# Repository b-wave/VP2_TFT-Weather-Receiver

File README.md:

# VP3-Weather-Receiver
*Davis Vantage Pro Weather Station Reciever using a Moteieino board with RFM69 and Color TFT Display.(1)*

This project is mainly a demo of the dekay/DavisRFM69 library (et.al.) @dekay using a TFT LCD screen 
it was intended to be a low-cost replacement for a broken Davis Vu Weather station that the ISS still works (with a few issues) 
*...but that is another story.* Hopefully *someone* will find this useful. I had a fun time developing it and
you can still see the saga of revisions in the source code listing as it evolved over several months. 

Display in action - Front view

Because i used a low cost Motieno, https://lowpowerlab.com/ it ran out of memory so this version
can display mainly only the data received from the Davis Vantage Vu ISS.
With some derived info like,  max and mins, rain, and cool TFT wind compass displays. 

Curently, this project version does not  add the internal data to make a complete 
TFT console replacement for display of all weather parameters. I had to remove
indoor temp, humidity and barometric pressure to make a usable replacement. 

I designed a circuit board and added some usefull features such as push button setting
a LiPo battery backup and charger, and a real time clock.  Some features will need to move to
the: *next version that uses a Teensey 3.2 board will do all this and more!*

## CREDITS:
This is a derivitive work from several authors i give credit
to the original works in line as i use them, without their work
this would not be possible.  The original work here includes the
additions for using TFT LCD displays. But I credit to getting the 
TFT to work with the RFM69 was because of this excellent article:
 https://www.pjrc.com/better-spi-bus-design-in-3-steps/  
 Thanks Paul! @PaulStoffregen

https://github.com/kobuki/VPTools
VPTools is a Davis(TM) weather station compatible transceiver library. 
It is a work in progress. It can receive from multiple RF transmitters (ISS, ATK, etc.) 
It tries to serve as a basis for similar hobby projects. 
Example sketches provide simple, parseable and RAW packet output among others.

https://github.com/dekay/DavisRFM69  By DeKay
Licence: Creative Commons Attribribution Share-Alike License http://creativecommons.org/licenses/by-sa/3.0/
This library is a modified version of the LowPowerLab's RFM69 library that enables reception of weather data 
from a Davis Instruments Integrated Sensor Suite (ISS) weather station.

https://github.com/LowPowerLab/RFM69  By Felix Rusu, LowPowerLab.com 
RFM69 library for RFM69W, RFM69HW, RFM69CW, RFM69HCW (semtech SX1231, SX1231H) 
Licence:GPL 3.0, please see the License.txt file for details. 
Be sure to include the same license with any fork or redistribution of this library.

ADAFRUIT Libraries and awesome info:
Written by Limor Fried/Ladyada for Adafruit Industries. MIT license, 
Licence : MIT https://github.com/adafruit/RTClib/blob/master/LICENSE
https://github.com/adafruit

https://github.com/adafruit/RTClib
This is a fork of JeeLab's fantastic real time clock library for Arduino.

These libraries are for the Adafruit ILI9341 display products:  
https://github.com/adafruit/Adafruit_ILI9341
https://github.com/adafruit/Adafruit-GFX-Library

## Notes:
1. The VP3 refernce to the never produced color LCD console from Davis Instrumnents https://www.davisinstruments.com/weather-monitoring/
that all of us fans of thier products wish for.

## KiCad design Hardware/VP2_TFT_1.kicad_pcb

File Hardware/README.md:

*Davis Vantage Vu Weather Station Reciever using a Moteieino board with RFM69 and Color TFT Display*

This folder provides the hardware info for this project. The circuit board in the main page picture is an early version.  The current board will be available on OSH Park so you can just order boards if you want them as-is.  The main differences are some minor circuit fixes, a slight size adjustment (to fit in a case I have in mind for the station) and embedding the RTC and battery on the board.  The original PCB was ony intended to use plug in modules and make it a little more robust than protoboards.  From the software, which is pretty ugly, you can probabily tell I am not a software expert, but this board has a strange combo of thru-hole and SMT technologies that reflect mostly what was on hand or could get easily for this proto. is not making the hardware hall of fame either, but it works.   

# Schematic

The schematic is in KiCAD format, here it is as a .JPEG if you don't have that software. You will notice a lot of hardware features on the board are not in use in the VP3 console receiver project due to program storage space *(1)*.  If you order the boards from [OSH Park](https://oshpark.com/)  you get 3 boards so one can programmed to be a console, one can be a logger, and the third can be an APRS packet generator/controller.  ISS does not care how many receivers are listening! 

The circuit board is shown assembled in these 3D renderings.  The circuit board will accomodate 2 sizes of 320x240 displays. The 3D renderings also show the assembly with the smaller 2.2" display.  You can see the outline of the optional 2.8" display and that i Put the LED indicators outside its outline. The LiPo battery connector is on this side as well as it is sandwiched in between the display and main PCB.  There are 3 tactile switches:
**"+"  "-"  "GO!"**
Used to set the clock and other parameters. You may want to use the long plunger types (13mm - 15mm)  should reach thru a front or rear panel in this configuration especially if you are putting it in some sort of case. They can be mounted on either side of the board as well.  With the 2.8" display the swithes will need to be relocated as they are blocked from the front by that display. *(2)*

The back side is where the Moteino and other modules plug in. The power connectors are on the left side.  I used a mini-USB connector for just power.  The Pin out for the USB_Power_Only is setup to match the SPARKFUN Breakout board 
[BOB-09966](https://www.sparkfun.com/products/9966) enables a power plug to be moved depending on the case requirements. 

# Circuit Description

The  [Parts List](https://github.com/b-wave/VP2_TFT-Weather-Receiver/blob/master/Hardware/VP2_TFT_1.xlsx) is generated from the schematics, the format is wierd.  Not all parts are installed depending of software support and features. You may want to read through these circuit descriptions before getting parts. I also did not provide much specific supplier information yet, except for the few noted, the others are fairly common parts you can order from [Digikey](https://digikey.com) or [Mouser](https://mouser.com) or other simular suppliers. I may supply a complete parts list with suppliers used on OSH Park that are compatible with the version of board. 

* **Arduino.** The brains of this project is the **Low Power Lab** [Moteino](https://lowpowerlab.com/shop/product/99)  Remember when ordering that you must add the RFM69CW 868/916MHz RF Module option or you won't be receiving any data!  You can also get the RFM69HCW but that version has more transmit power that you really don't need for this project since we never transmit anything. Also, you can add the headers and possibly the memory chip but can use the on-chip non-volitile memory in the software. It come with a simple wire antenna that actully works OK. There is also a small $2.00 [915 MHz Helical Antenna](https://lowpowerlab.com/shop/product/160?search=antenna) you may consider ordering as well. Speaking of antennas, I went full up with a real ISM band rubber ducky antenna, that works fantasctic! But when is a good thing *too good?*  When you receive a neighbor's ISS, *from blocks away,* which seems not a big issue until you recive a rain count from it...it causes an erronious rain indication. For signal, the Motieno receiver decodes comfortably down to about -90dBm by my observations. If all else fails...there is a reset button (S4) that will restart the software.  This actully comes in more handy as the battery is always connected and you can't easily power cycle the unit. 

* **TFT Display.** The part that makes this a [Davis Vantage Vu](https://www.davisinstruments.com/solution/vantage-vue/) console is the TFT color LCD display. I used the ones that feature the ILI9341 chip in 240x320 QVGA resolution.  It turns out they that come in two sizes that work on the same software (see image below).  These are very common on e-bay and Amazon if you match the pinouts it should plug into the board just fine.  In the final version I intend to use the **Adafruit** versions for supply chain longevity i don't think the China clones will have. If you use the ones I found then thes will plug into the PCB directly.  You can jumper in others but if you want to use my software without modificaiton you need ILI9341 and 240x320 to be compatible. The two boards  used are 2.8" TFT SPI 240x320 v1.1 TJCTM24028-SPI and the smaller 2.2" CR2013-M12420 (the 2.2" version is shown in the pics).  Backlight is provided by white LEDs in the display. Reistor R4 sets the current to control the max brightness.  A PWM dimmer comprised of Q1 (NPN Transistor) R14 base resistor (10K) controled by one of he PWM pins (D3).  Note: R20 (100k) provides a pull up to keep the transistor turned on, even if D3 is not active in hi Z (input) state. The value from the AMBIENT Sensor can be used to dim the backlight. This sensor is described in the SENSORS section.  In a dark room, at full brightness, the LED puts out a lot of light!  The other reason we need to be able to dim it is for power savings on battery power, LEDs take a lot of current. If you want the display backlight on, set the brightness with R4, solder short the jumper J1, (see: JUMPERS) and DNI Q1, R14, and R20. Note: I did not see any noticable degredation in the RF perfomace while the PWM was running.  

[Two compatible TFT display boards]

* **SD Card.** The other feature of these TFT Displays is both have SPI controlled SD card sockets. I intended to use these as a data logging feature, but the current software does not support it. Also, in reading complaints and warnings about using these display SD cards I suspect there are SPI circuit issues so I added two buffer chips to try to eliminate these issues. The two 74AHC1G125 single-package gates U1 and U3 to only allow SPI traffic when the cards are specifically selected via the chip selet pin. This hardware will hopefully keep the SD cards from getting corrupted. To bypass these chips if it turns out we don't need to install the buffer(s), JP1 and JP2 will povide a non-switched path by soldering them closed with a blob of solder. LED D5 "ACTY" and R19 can be added to monitor the SD card activity. At this time the hardware and the logging feature have not been tested.

* **RTC.** The original prototype used a RTC on a board. This is easy to breadboard with but takes a lot of board space and height. I thought it would be OK, considering the Motieno is on a socket too, but decided to try an embedded approach in this version using a compact **SO-8**  *-z*  version of the **DS3231Z chip**.  Time is backed up by a coin cell (BT1).  See Batteries section.
* **Sensors.**  Several on board sensors and conectors for sensors are provided.  
  * **Voltage sensor.** Consists of two high-value resistors (100k) R10 and R11 Take the input voltage of the battery and divide it in half. Capacitor C2 can be used for smoothing or noise reduction if needed, this signal is fed into VBATT (Analog Pin A7).  The voltage is scaled and is currently only used as a display of the battery voltage as a charge indication. 
  * **Ambient Sensor.**  An analog voltage proportional to the ambient light is provide by a voltage divider formed by R16 a **LDR** and scaled by R16 (100k). A capacitor (C10) is provided to smooth the voltage input. The sensor used was harvested from a broken lawn solar light. 
  * **Indoor Humidity and Tempature Sensor.**  J7 provides a pin compatible connector for this sensor. It has a unique interface provided into pin D2 with a 4.7K pull up (R21)  These integrated temp/humidity sensors are pretty common on Amazon and other suppliers.  This was only used in early code versions before i relized there would not be enough code storage space on the Moteuino board. 
  * **Barometric Sensor.** J8 is an i2C connector arranged with voltage and ground pins to match an  I2C mems barometer breakout board, alas, i did not have code space to keep it.  Pins A5 and A4 provide the i2C SCL and SDA signals. Any other I2C board can work with these pins as well. 
* **LEDs.** Several LEDs indicators are also sprinkled around the board, mostly for debugging, and what fun is having no blinking lights?

LED| Label | Function
------------ | ------------ | -------------
D1| CHARGE | MCP73831 STAT Pin "Charging"
D3| Red |  Controlled by Pin A3, flashes for bad stuff
D4| Green |Controlled by Pin D9 (same as Motieno LED) good stuff
D5| ACTY | Controlled by Pin D4 to show some status? Maybe as SD card issues?
D6| Yellow | (DNI) TP6 connect if needed for debug, visible from front panel 
D7| SD_CS | on if SD Card chip is selected (SPI activity)

* **Back up Batteries.**  
Two battery circuits are provided for back up purposes. 

  * **Main Power** The provided battery charger circuit is intended to keep the main battery charged and take over in the event of a power failure or if you just want to move the receiver around.  It keeps the Max/Mins and rain totals in memory as well. The charge controller is a (U2) MCP73831.   An and old cell phone battery was used with a soldered JST type battery pigtail from [Adafruit](https://www.digikey.com/product-detail/en/adafruit-industries-llc/1131/1528-1494-ND/5761282?utm_adgroup=Accessories&utm_source=google&utm_medium=cpc&utm_campaign=Shopping_Product_Development%20Boards%2C%20Kits%2C%20Programmers_NEW&utm_term=&utm_content=Accessories&gclid=EAIaIQobChMIx6-Q28GF6gIVEQnnCh3sRQ0aEAQYASABEgJNKPD_BwE). It  but it fit nicely between the board and display and holds a charge long enough. I did not connect the other pad(s)on the battery, which is probabily a thermistor or battery ID pin, which is not needed in this circuit only "+" and "-". The battery connector BATT (J1) is a standard JST_PH_B2B-PH-K_1x02_P2.00mm_Vertical common for batteries and is polarized. 
  
[Battery figure here?]

The charging current is set by R13.  For this application, a large (10K or larger) resistor should be used to just maintain the battery charge at 100mA or even less, I used an old battery, that may now suck as a cell phone battery, but it is only intended to run for *a few hours at most* and is not intended to be a portable device *per se*, so a slow charge is fine. When the battery is charging LED (D1) is on and turns off when a full charge is reached. Input power (5V) comes from J2 or J3 and the battery takes over when the supply is unplugged or interrupted. An MBRA140 SHOTTKY Diode (D2) diode switches depending on the voltage difference of Vin and Vbatt. The voltage sensor (described in the Sensors Section) circuit can be used to monitor the voltage on the batery to let you know when it it time to plug in, but we only use that for display.  

Also, two PTC fuses are provided (F1, F2) to protect the circuits. F1 is a .5A PTC resettable fuse that protects the circuitry when powered by an external power supply from (J2 or J3). F2 is in-line with the battery from  (J1)  in case there is too much current from the battery. F1 is the most importaint as the console is intended to be plugged in most of the time.  F2 is only if there is a battery issue, which is an unlikely possibility, but if the device is dropped or worse yet stepped on which can cause a short and these little batteries contain a lot of energy. If you do accidentally trip one of these they heat up and essentally open then reset themselves when they cool down. 
  * **RTC Backup**  BT1 is the RTC back up. I  reduced the battery from the standard **CR2023** 3V Li Coin cell to a smaller **CR1220**.  I am not sure how long this cell will last, but that is only really needed if the main power *and* the battery back up fails as well.  The holder is soldered to the circuit board.
  
* **Connectors and Misc.**  Here are descriptions of the various connectors, jumpers, and test points on the board. Various *"solder blob"* configuraton jumpers (JP) are on the board to bypass or enable some features.  Pin D2 is selectabe between one of two features, shown below I don't think both will be usable at the same time so it is an either/or selecton for it

ITEM | Label | Type |Function
----- | -------- | ------------ | -------------
J1| BATT | 2-pin JST | LiPo Battery 
J2 | USB_POWER_ONLY  | Header, 5-Pin, 0.1"  | SparkFun USB Breakout board (+5V, GND No data pins)
J3 | USB-B POWER  | USB Mini-B, SMT | USB VBUS Power Only (+5V,  GND  No Data pins) 
J4 | EXTERNAL ANTENNA  | U.FL RF COAX  | Connects Board to Moteino Antenna 
J5 | EXTERNAL ANTENNA   | SMA (R-P or NORM)   | Antenna Connector
J6 | GPS/APRS  | Header, 4-Pin, 0.1"  | Serial data (D0, D1 ) + 3.3V Power + GND
J7 | DHT-11   | Header, 4 Pin 0.1"  | Humidity and Temp Sensor 
J8 | I2C  | Header, 4-pin 0.1"   | Baro Sensor or other I2C, SCL SDA 3.3V POWER GND
JP1 | NO PWM  |  SMT Jumper | To Bypass Backlight PWM Transistor Q1
JP2 | NO SI BUFF   | SMT Jumper  | Bypass MOSI Switch  U3 to SD Card
JP3 | NO SO BUFF   | SMT Jumper |  Bypass MISO Switch U1 from SD Card
JP4 | N/A   | N/A   | Not used - removed from board version
JP5 | IRQ   | SMT Jumper   | Connects RTC IRQ to pin D2
JP6 | CARD DET  | SD card inserted  | No card = low Connects to pin D2
TP1 | 32KHZ  | Test Point  | RTC 32KHz Output
TP2 | SQW  | Test Point  | RTC Square Wave Output (for interrupt)
TP3 | LED  | Test Point  | Moteino LED Signal (D9)
TP4 | GND  | Test Point  | Power / Test Ground
TP5 | VBATT | Test Point  | Battery Voltage
TP6 | TST  | Test Point  | Connetct a digital signal to LED6 ( or Peizo Speaker!) 
TP7 | /RST   | Test Point  | RTC Reset, GND = Resets RTC clock

 * **NOTES** 
   * *1.  I have started a version that uses a Teensey 3.2 for more software space.  Early versions show promise as it now sucessfully communicates to the RF-69 radio and TFT.*
   * *2. The 2.8" display has a touch screen but the pins are not connected in in this version.*

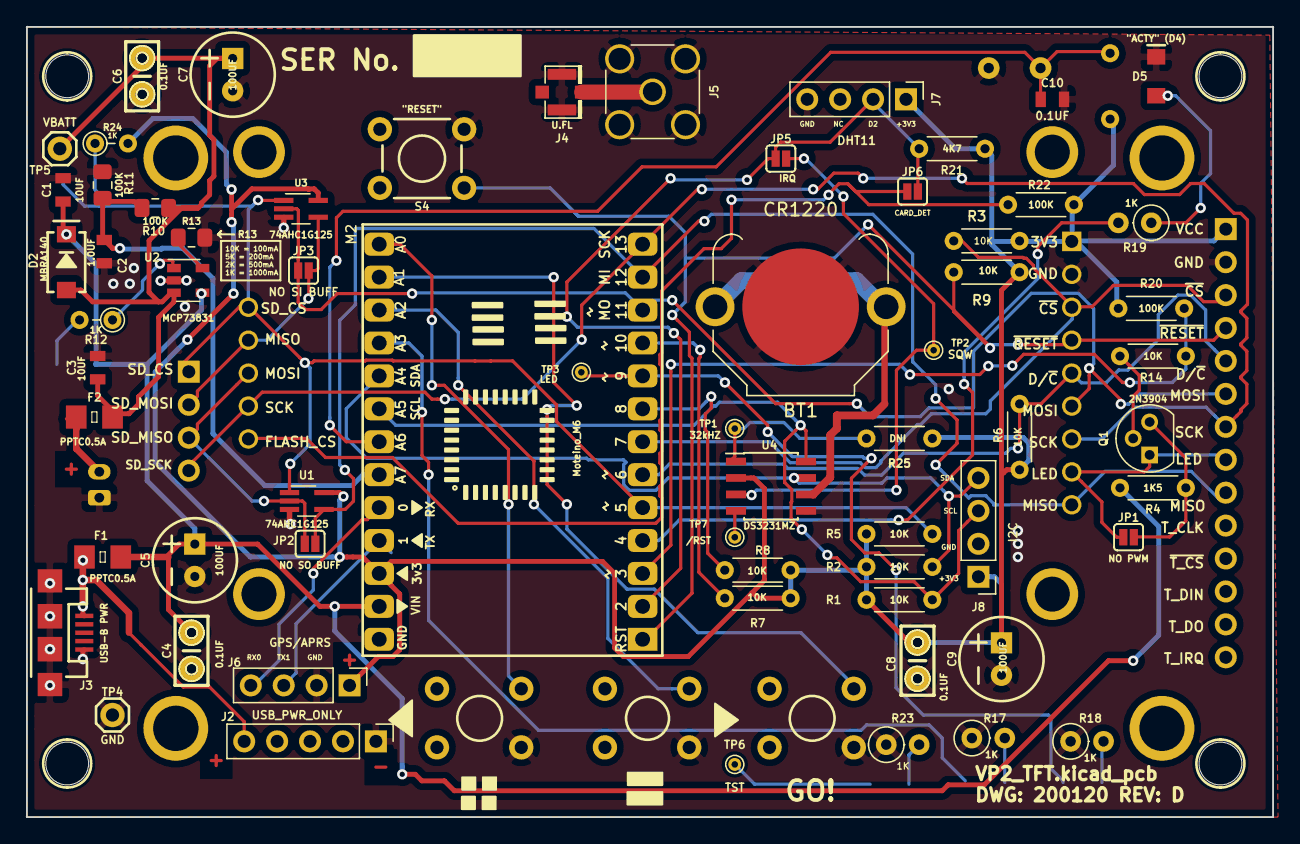
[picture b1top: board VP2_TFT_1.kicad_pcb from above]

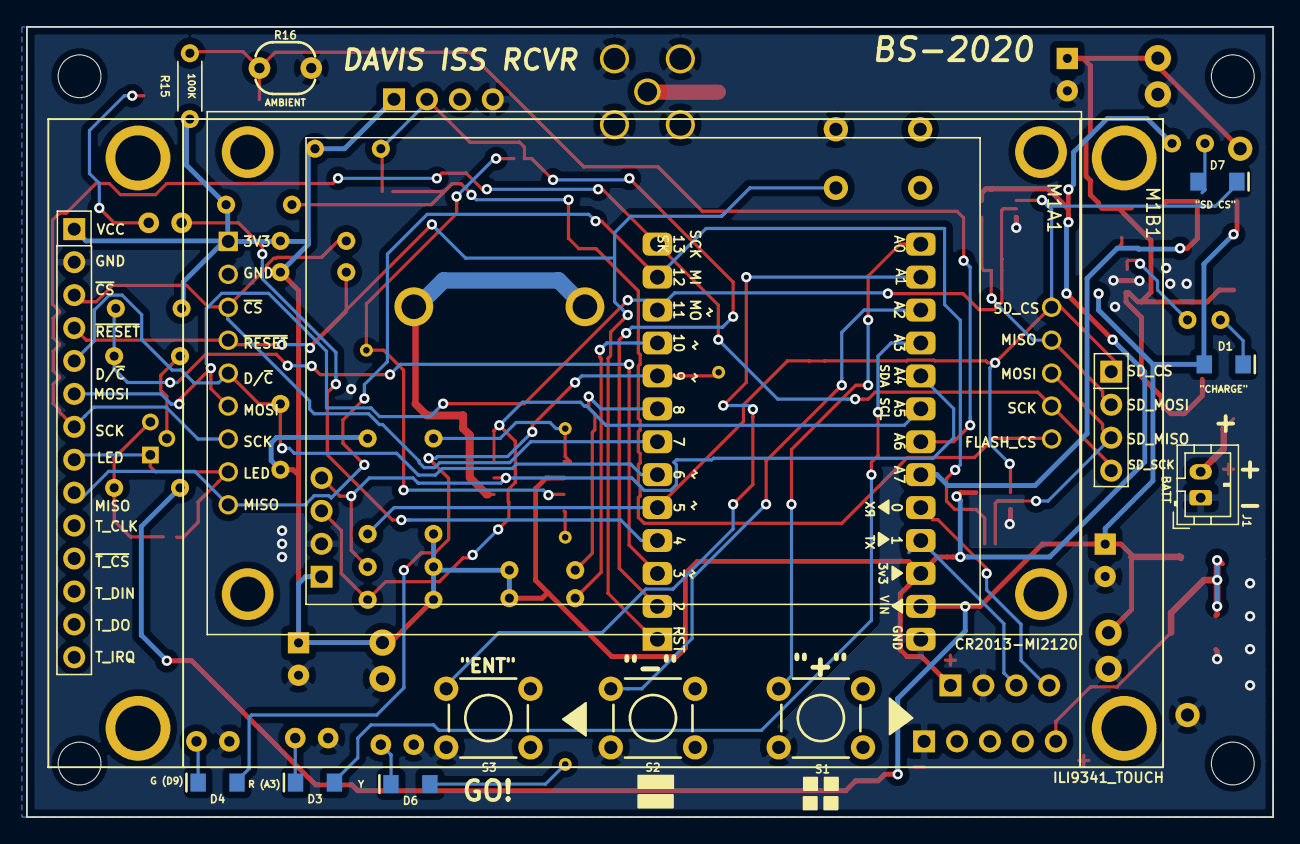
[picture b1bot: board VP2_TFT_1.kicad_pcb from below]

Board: 2 copper layers, 96.1 x 61.0 mm, 81 parts (13 on the bottom side), 49 nets.

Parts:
BT1: CR1220; BatteryHolder_Keystone_3001_1x12mm
C1, C3: 10UF; 0805
C2: 1.0UF; 0805
C4, C6, C8: 0.1UF; CAP-PTH-SMALL-KIT
C5, C7, C9: 100UF; CPOL-RADIAL-2.5MM-6.5MM
C10: 0.1UF; 0805
D1: "CHARGE"; LED-1206
D2: MBRA140; SMA-DIODE
D3: R (A3); LED-1206
D4: G (D9); LED-1206
D5: "ACTY" (D4); LED-1206
D6: Y; LED-1206
D7: "SD CS"; LED-1206
F1, F2: PPTC0.5A; 1206
H1, H2, H3, H4: STAND-OFF
J1: BATT; JST_PH_B2B-PH-K_1x02_P2.00mm_Vertical
J2: USB_PWR_ONLY; PinHeader_1x05_P2.54mm_Vertical
J3: USB-B PWR; USB-MICROB
J4: U.FL
J5: SMA; SMA_Amphenol_132291-12_Vertical
J6: GPS/APRS; PinHeader_1x04_P2.54mm_Vertical
J7: DHT11; PinHeader_1x04_P2.54mm_Vertical
J8: I2C; PinHeader_1x04_P2.54mm_Vertical
JP1: NO PWM; SMT-JUMPER_2_NO_SILK
JP2: NO SO BUFF; SMT-JUMPER_2_NO_SILK
JP3: NO SI BUFF; SMT-JUMPER_2_NO_SILK
JP5: IRQ; SMT-JUMPER_2_NO_SILK
JP6: CARD_DET; SMT-JUMPER_2_NO_SILK
M1A1: CR2013-MI2120
M1B1: ILI9341_TOUCH; ILI9341_TFT_TOUCH
M2: Moteino_M6; MoteinoM6
Q1: 2N3904; TO-92
R1, R2, R3, R5, R6, R7, R8, R9, R14: 10K; R_Axial_DIN0204_L3.6mm_D1.6mm_P5.08mm_Horizontal
R4: 1K5; R_Axial_DIN0204_L3.6mm_D1.6mm_P5.08mm_Horizontal
R10, R11: 100K; R_0805_2012Metric_Pad1.15x1.40mm_HandSolder
R12, R24: 1K; R_Axial_DIN0204_L3.6mm_D1.6mm_P2.54mm_Vertical
R13: R13; R_0805_2012Metric_Pad1.15x1.40mm_HandSolder
R15, R20, R22: 100K; R_Axial_DIN0204_L3.6mm_D1.6mm_P5.08mm_Horizontal
R16: AMBIENT; PHOTOCELL
R17, R18, R19, R23: 1K; R_Axial_DIN0207_L6.3mm_D2.5mm_P2.54mm_Vertical
R21: 4K7; R_Axial_DIN0204_L3.6mm_D1.6mm_P5.08mm_Horizontal
R25: DNI; R_Axial_DIN0204_L3.6mm_D1.6mm_P5.08mm_Horizontal
S1: "+"; TACTILE_SWITCH_PTH_6.0MM
S2: "-"; TACTILE_SWITCH_PTH_6.0MM
S3: "ENT"; TACTILE_SWITCH_PTH_6.0MM
S4: "RESET"; TACTILE_SWITCH_PTH_6.0MM
TP1: 32kHZ; TestPoint_THTPad_D1.0mm_Drill0.5mm
TP2: SQW; TestPoint_THTPad_D1.0mm_Drill0.5mm
TP3: LED; TestPoint_THTPad_D1.0mm_Drill0.5mm
TP4: GND; 1X01
TP5: VBATT; 1X01
TP6: TST; TestPoint_THTPad_D1.0mm_Drill0.5mm
TP7: /RST; TestPoint_THTPad_D1.0mm_Drill0.5mm
U1, U3: 74AHC1G125; SOT-353_SC-70-5_Handsoldering
U2: MCP73831; SOT-23-5
U4: DS3231MZ; SOIC-8_3.9x4.9mm_P1.27mm

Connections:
+3V3: C8.1, C9.1, J6.1, J7.1, J8.1, M1A1.1, M1B1.1, M2.24, R1.1, R2.1, R3.1, R5.1, R6.1, R7.1, R8.1, R9.1, R15.1, R20.1, R21.1, R22.2, R24.2, R25.1, U1.5, U3.5, U4.2
+BATT: C3.1, C6.1, C7.1, D2.A, F2.2, R10.1, TP5.1, U2.3
/CD: JP6.1, M1A1.14, R22.1
/IRQ: JP5.2, TP2.1, U4.3
/MISO: JP2.2, M1A1.9, M1B1.9, M2.12, U1.4
/MOSI: JP3.1, M1A1.6, M1B1.6, M2.11, U3.2
/PB1: M2.14, S1.1
/PB2: M2.16, S2.1
/PB3: M2.15, S3.1
/SCK: M1A1.7, M1A1.13, M1B1.7, M1B1.18, M2.13
/SD_MISO: JP2.1, M1A1.12, M1B1.17, U1.2
/SD_MOSI: JP3.2, M1A1.11, M1B1.16, U3.4
/SENSOR: C10.1, M2.20, R15.2, R16.1
/TFT_LED: JP1.1, M1A1.8, M1B1.8, Q1.1
/Vin: F1.1, J2.5, J3.VBUS
/~RESET: M1A1.4, M1B1.4, M2.1, R9.2, S4.1
/~SD_CS: D7.C, M1A1.10, M1B1.15, M2.5, R5.2, U1.1, U3.1
/~TFT_CS: M1A1.3, M1B1.3, M2.7, R3.2
/~TFT_DC: M1A1.5, M1B1.5, M2.6, R6.2
D0: J6.4, M2.22
D1: J6.3, M2.23
D2: J7.2, JP5.1, JP6.2, M2.2, R21.2
GND: BT1.2, C1.2, C2.2, C3.2, C4.2, C5.2, C6.2, C7.2, C8.2, C9.2, C10.2, D5.C, J1.1, J2.1, J3.GND, J3.MT1, J3.MT2, J3.P$1, J3.P$2, J4.1, J4.2, J5.2, J6.2, J7.4, J8.2, M1A1.2, M1B1.2, M2.26, R11.2, R13.2, R16.2, R17.1, R18.1, R23.1, S1.3, S2.3, S3.3, S4.3, TP4.1, U1.3, U2.2, U3.3, U4.5
LED_G: D4.A, M2.9, TP3.1
LED_R: D3.A, M2.17
unnamed: BT1.1, U4.6
unnamed: D1.C, R12.2
unnamed: D3.C, R17.2
unnamed: D4.C, R18.2
unnamed: D5.A, R19.1
unnamed: D6.A, TP6.1
unnamed: D6.C, R23.2
unnamed: D7.A, R24.1
unnamed: F2.1, J1.2
unnamed: J4.FEED, J5.1
unnamed: JP1.2, Q1.3, R4.2
unnamed: M2.4, R19.2
unnamed: M2.8, R8.2
unnamed: M2.10, R7.2
unnamed: Q1.2, R14.1
unnamed: R12.1, U2.1
unnamed: R13.1, U2.5
unnamed: R25.2, TP1.1, U4.1
unnamed: TP7.1, U4.4
PWM: M2.3, R14.2, R20.2
SCL: J8.3, M2.19, R1.2, U4.8
SDA: J8.4, M2.18, R2.2, U4.7
VBAT: C2.1, M2.21, R10.2, R11.1
VBUS: C1.1, C4.1, C5.1, D1.A, D2.C, F1.2, M2.25, R4.1, U2.4

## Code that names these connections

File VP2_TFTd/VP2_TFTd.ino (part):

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//TODO: Include SD Card support for logging.

// For Mote (R6)Use hardware SPI like on Uno, #13, #12, #11) and the below for CS/DC
#define TFT_DC  6             // was 9
#define TFT_CS 7              //was 10

//Clock
#include <RTClib.h>           //Using Adafruit: https://github.com/adafruit/RTClib
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///Enable the buttons for settings
#include <Button.h>  //V1.12

Button PLUS_key(A0);  // PB1 V13 Was A1
Button MINUS_key(A2); // PB2
Button OK(A1);        // PB3 V13 Was A0

/*  This is the PIN info for the V2 PROTOTYPE REV D HARDWARE DWG 200118 
 *   
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 * A5 = SCL
 * A4 = SDA
 * A6 = AMBIENT LIGHT SENSOR
 * A2 = PB2 (-)
 * A0 = PB1 (+)
 * A1 = PB3 (GO!)
 * 
 * D2 = SQW (int) SD Card + Derect 
 * A3 = LED (D3)  LED_R 
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 // Serial.println(DrawCompass());  //output  status too
  DrawCompass();
   
  pinMode(TFT_CS, OUTPUT);  //V1.04 ---make sure the SPI buss knows who is boss?
  digitalWrite(TFT_CS, HIGH);
  pinMode(SS_PIN_RADIO, OUTPUT);  //V1.04 ---
  digitalWrite(SS_PIN_RADIO, HIGH);
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
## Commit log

2020-06-11 Documents
2020-06-11 Adding pictures and some formatting
2020-06-11 fixed typos and more edits
2020-06-11 more typoes - learn to spell
2020-06-11 added Davis Instruments and Low Power Labs URLs
2020-06-11 fixe typo
2020-06-11 typo
2020-06-11 added Paul and dekay mentions
2020-06-11 KiCad Schematics and PCB Files
2020-06-11 Added Schematic & 3D rendering
2020-06-11 added PCB 3D renderings
2020-06-11 Added link to Power connector
2020-06-11 Added Links to LowPower Lab and BOM
2020-06-12 Parts + BOM
2020-06-13 Edit Displays Section
2020-06-13 SD Card Circuit Descriptons
2020-06-13 RTC description
2020-06-13 adding emphasis!
2020-06-14 Modify Display circuits section
2020-06-14 Sensors sections added
2020-06-14 Sensor section format
2020-06-15 LED table added
2020-06-15 Added LiPo Battery description
2020-06-15 Display Pictures uploaded
2020-06-15 Updated Display Section
2020-06-16 Antenna Info
2020-06-16 Battery info updates
2020-06-16 Battery info updated
2020-06-16 Clean ups and added Connector Table
2020-06-16 Connectors, Jumpers, and Test points
2020-06-16 relocated jumper descriptions to "Misc." section
2020-06-17 Format BOM to PDF File
2020-06-17 Parts List PDF file update
    I Accidently added another /Hardware folder. Bunch of deletes fixed that.
2020-06-18 Dispaly image missing
2020-06-18 Re-loaded Displays Image
    Missing from extra files delete in wrong folder
2020-06-19 Changed BOM to .xlsx
    Easier to use than .pdf
2020-06-19 BOM Link to the .xlsx file
    https://github.com/b-wave/VP2_TFT-Weather-Receiver/blob/master/Hardware/VP2_TFT_1.xlsx
2020-06-19 Update Board description.
2020-06-20 Battery description
2020-06-24 Typos and added note for new Teensey 3.2 version
2020-06-24 Note 2 was before note 1
2020-07-17 Create Demo_artificial_horizon_9.ino
    Recovered file...need to move to JeepOmeter Project
2020-08-08 New V1.13 - board supported
    New Hardware Use with VP2TFT.kicad.pcb DWG 200118 REV D or later.
    (a) TODO - New pin assignments - Done!
    (b) TFT Rotated 180 from proto - DONE!
    (c) Reduce Backlight on battery power
    (d) Improved wind direction indicator smoothing (north crossing and fast(er) large jumps)
